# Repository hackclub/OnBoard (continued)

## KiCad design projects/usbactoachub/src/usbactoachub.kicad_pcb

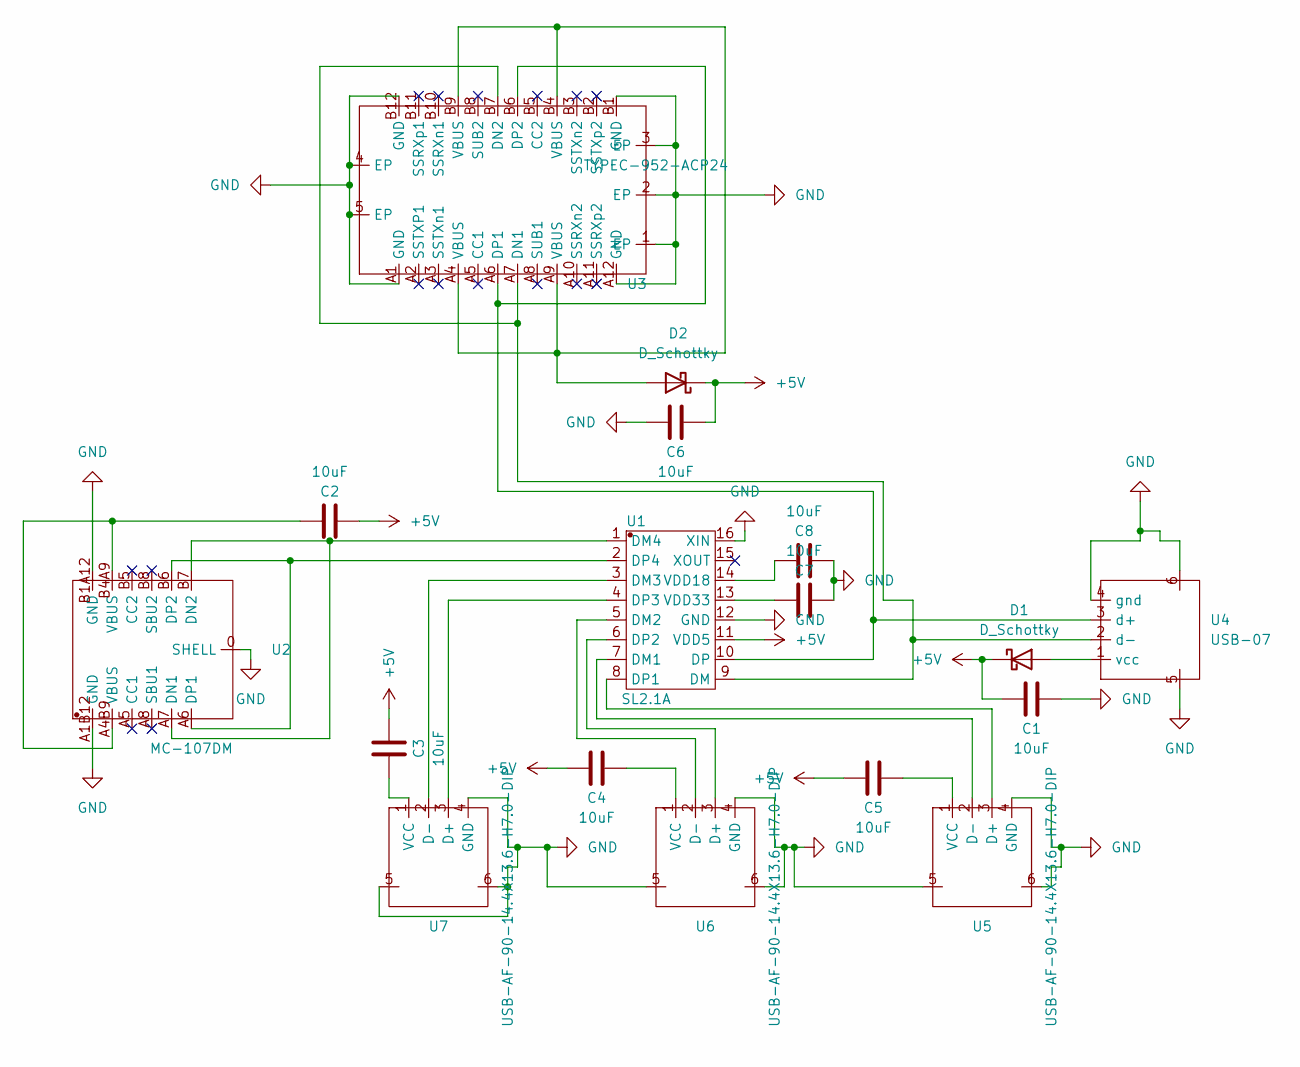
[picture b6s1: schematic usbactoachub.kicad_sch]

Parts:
C1, C2, C3, C4, C5, C6, C7, C8: 10uF; C0603; LCSC Part # C19702
D1, D2: D_Schottky; SOD-323_L1.8-W1.3-LS2.5-RD; LCSC Part # C48192
U1: SL2.1A; SOP-16_L10.0-W3.9-P1.27-LS6.0-BL; LCSC Part # C192893
U2: MC-107DM; USB-C-SMD_MC-107DM; LCSC Part # C2874569
U3: TYPEC-952-ACP24; USB-C-SMD_TYPEC-952-ACP24; LCSC Part # C2840398
U4: USB-07; USB-A-SMD_USB-07; LCSC Part # C183610
U5, U6, U7: USB-AF-90-14.4X13.6-H7.0-DIP; USB-A-TH_C46407; LCSC Part # C46407

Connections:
+5V: C1.2, C2.2, C3.1, C4.2, C5.2, C6.1, D1.1 (K), D2.1 (K), U1.11 (VDD5)
GND: C1.1, C6.2, C7.2, C8.2, U1.12 (GND), U1.16 (XIN), U2.0 (SHELL), U2.A1B12 (GND), U2.B1A12 (GND), U3.1 (EP), U3.2 (EP), U3.3 (EP), U3.4 (EP), U3.5 (EP), U3.A1 (GND), U3.A12 (GND), U3.B1 (GND), U3.B12 (GND), U4.4 (gnd), U4.5, U4.6, U5.4 (GND), U5.5, U5.6, U6.4 (GND), U6.5, U6.6, U7.4 (GND), U7.5, U7.6
unnamed: C2.1, U2.A4B9 (VBUS), U2.B4A9 (VBUS)
unnamed: D1.2 (A), U4.1 (vcc)
unnamed: D2.2 (A), U3.A4 (VBUS), U3.A9 (VBUS), U3.B4 (VBUS), U3.B9 (VBUS)
unnamed: U1.7 (DM1), U5.2 (D-)
unnamed: U1.5 (DM2), U6.2 (D-)
unnamed: U1.3 (DM3), U7.2 (D-)
unnamed: U1.1 (DM4), U2.A7 (DN1), U2.B7 (DN2)
unnamed: U1.9 (DM), U3.A7 (DN1), U3.B7 (DN2), U4.2 (d-)
unnamed: U1.8 (DP1), U5.3 (D+)
unnamed: U1.6 (DP2), U6.3 (D+)
unnamed: U1.4 (DP3), U7.3 (D+)
unnamed: U1.2 (DP4), U2.A6 (DP1), U2.B6 (DP2)
unnamed: U1.10 (DP), U3.A6 (DP1), U3.B6 (DP2), U4.3 (d+)
unnamed: C8.1, U1.14 (VDD18)
unnamed: C7.1, U1.13 (VDD33)
unnamed: C5.1, U5.1 (VCC)
unnamed: C4.1, U6.1 (VCC)
unnamed: C3.2, U7.1 (VCC)

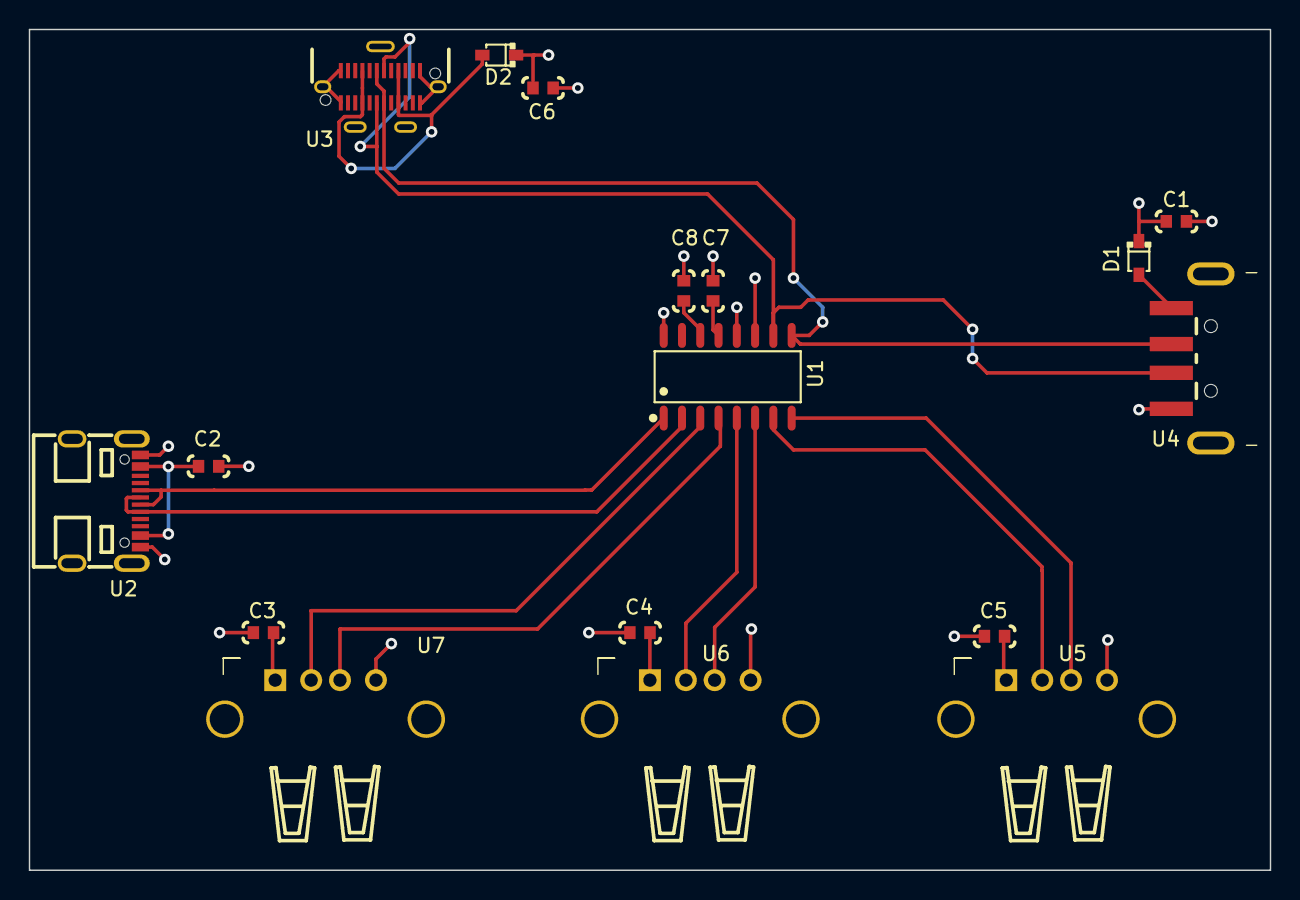
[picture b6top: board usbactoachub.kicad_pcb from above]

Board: 4 copper layers, 86.2 x 58.4 mm, 17 parts (0 on the bottom side), 20 nets.

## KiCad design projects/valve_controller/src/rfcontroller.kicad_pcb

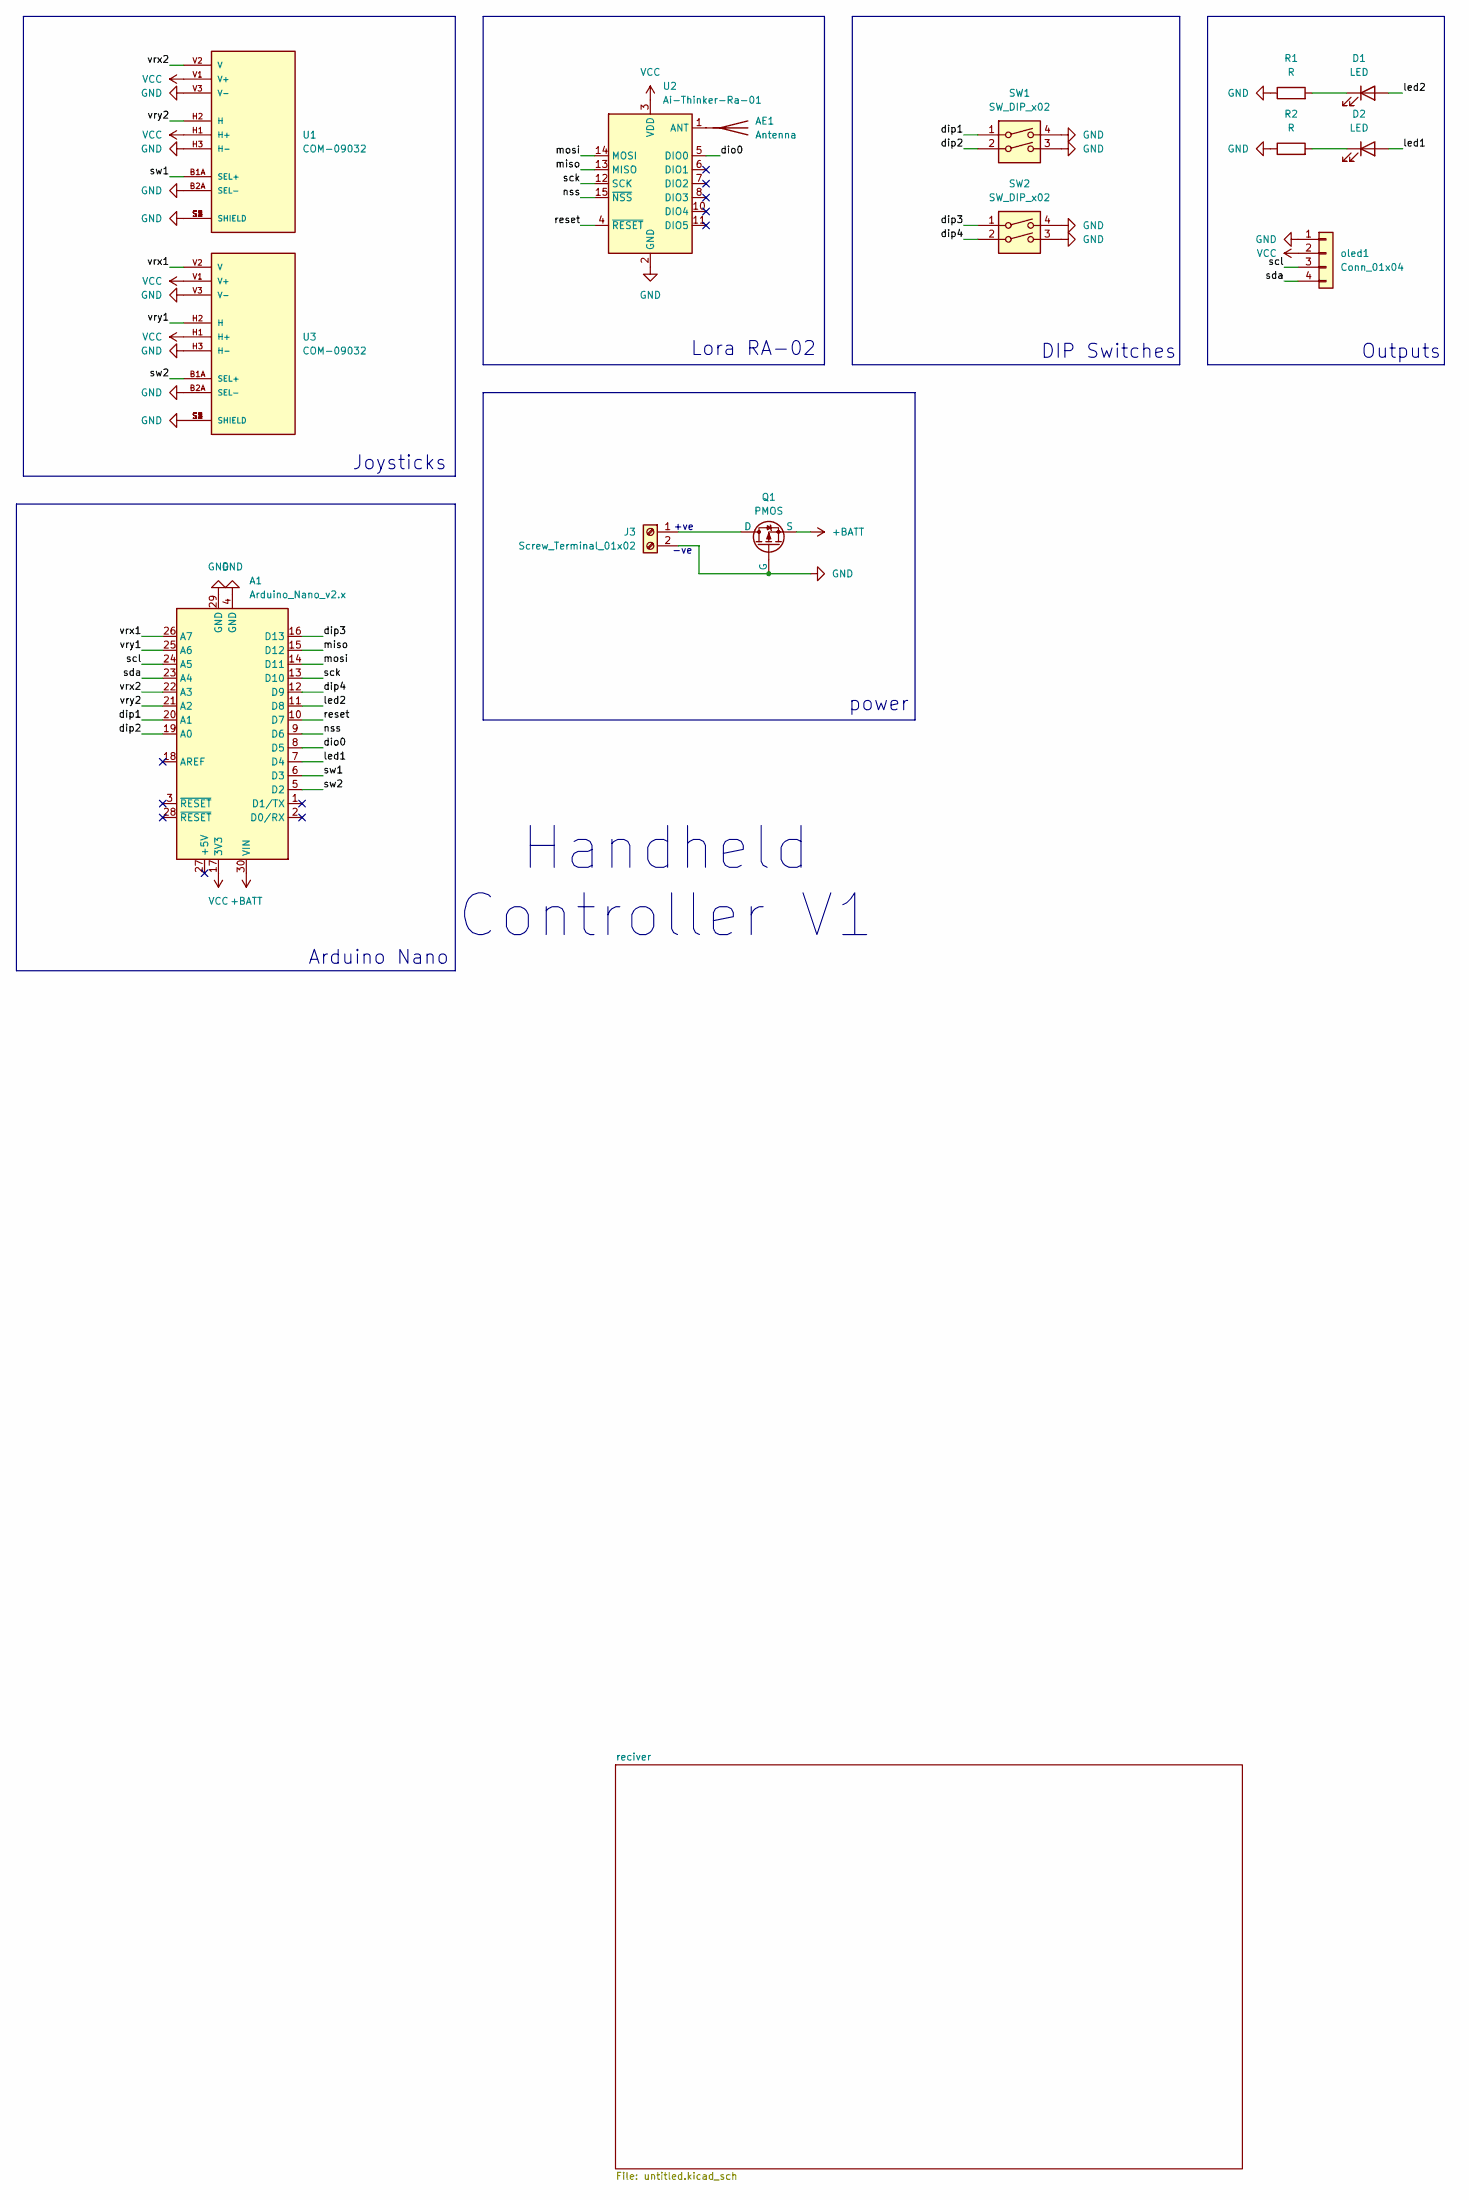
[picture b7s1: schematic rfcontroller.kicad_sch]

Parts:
A1: Arduino_Nano_v2.x; Arduino_Nano
AE1: Antenna; SMA_Amphenol_901-143_Horizontal
D1, D2: LED; LED_D3.0mm
J3: Screw_Terminal_01x02; TerminalBlock_Xinya_XY308-2.54-2P_1x02_P2.54mm_Horizontal
Q1: PMOS; TO-220-3_Vertical
R1, R2: R; R_Axial_DIN0204_L3.6mm_D1.6mm_P5.08mm_Horizontal
SW1, SW2: SW_DIP_x02; SW_DIP_SPSTx02_Slide_9.78x7.26mm_W7.62mm_P2.54mm
U1, U3: COM-09032; XDCR_COM-09032; PARTREV N/A
U2: Ai-Thinker-Ra-01; Ai-Thinker-Ra-01-LoRa_updated
oled1: Conn_01x04; PinHeader_1x04_P2.54mm_Vertical

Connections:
+BATT: A1.30 (VIN), Q1.3 (S)
/dio0: A1.8 (D5), U2.5 (DIO0)
/dip1: A1.20 (A1), SW1.1
/dip2: A1.19 (A0), SW1.2
/dip3: A1.16 (D13), SW2.1
/dip4: A1.12 (D9), SW2.2
/led1: A1.7 (D4), D2.2 (A)
/led2: A1.11 (D8), D1.2 (A)
/miso: A1.15 (D12), U2.13 (MISO)
/mosi: A1.14 (D11), U2.14 (MOSI)
/nss: A1.9 (D6), U2.15 (~NSS)
/reset: A1.10 (D7), U2.4 (~RESET)
/sck: A1.13 (D10), U2.12 (SCK)
/scl: A1.24 (A5), oled1.3
/sda: A1.23 (A4), oled1.4
/sw1: A1.6 (D3), U1.B1A (SEL+)
/sw2: A1.5 (D2), U3.B1A (SEL+)
/vrx1: A1.26 (A7), U3.V2 (V)
/vrx2: A1.22 (A3), U1.V2 (V)
/vry1: A1.25 (A6), U3.H2 (H)
/vry2: A1.21 (A2), U1.H2 (H)
GND: A1.4 (GND), A1.29 (GND), AE1.2, J3.2, Q1.2 (G), R1.1, R2.1, SW1.3, SW1.4, SW2.3, SW2.4, U1.B2A (SEL-), U1.H3 (H-), U1.S1 (SHIELD), U1.S2 (SHIELD), U1.S3 (SHIELD), U1.S4 (SHIELD), U1.V3 (V-), U2.2 (GND), U2.9 (GND), U2.16 (GND), U3.B2A (SEL-), U3.H3 (H-), U3.S1 (SHIELD), U3.S2 (SHIELD), U3.S3 (SHIELD), U3.S4 (SHIELD), U3.V3 (V-), oled1.1
unnamed: AE1.1 (A), U2.1 (ANT)
unnamed: D1.1 (K), R1.2
unnamed: D2.1 (K), R2.2
unnamed: J3.1, Q1.1 (D)
VCC: A1.17 (3V3), U1.H1 (H+), U1.V1 (V+), U2.3 (VDD), U3.H1 (H+), U3.V1 (V+), oled1.2

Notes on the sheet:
-ve
Lora RA-02
power
Joysticks
Handheld Controller V1
+ve
DIP Switches
Outputs
Arduino Nano

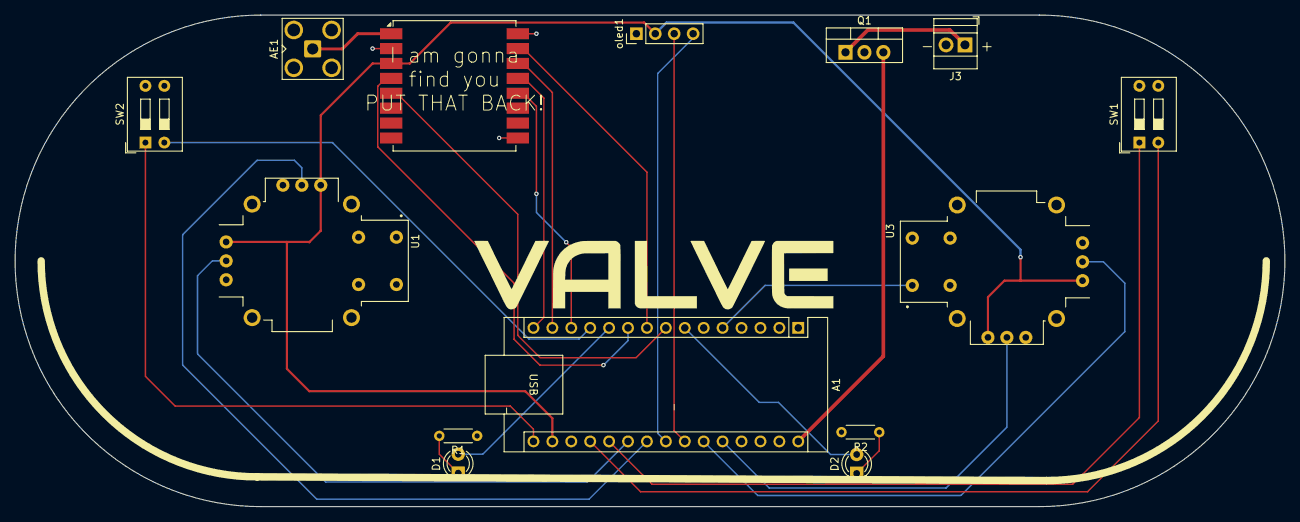
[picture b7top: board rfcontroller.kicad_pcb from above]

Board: 2 copper layers, 170.5 x 66.0 mm, 15 parts (0 on the bottom side), 27 nets.

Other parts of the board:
g: LOGO

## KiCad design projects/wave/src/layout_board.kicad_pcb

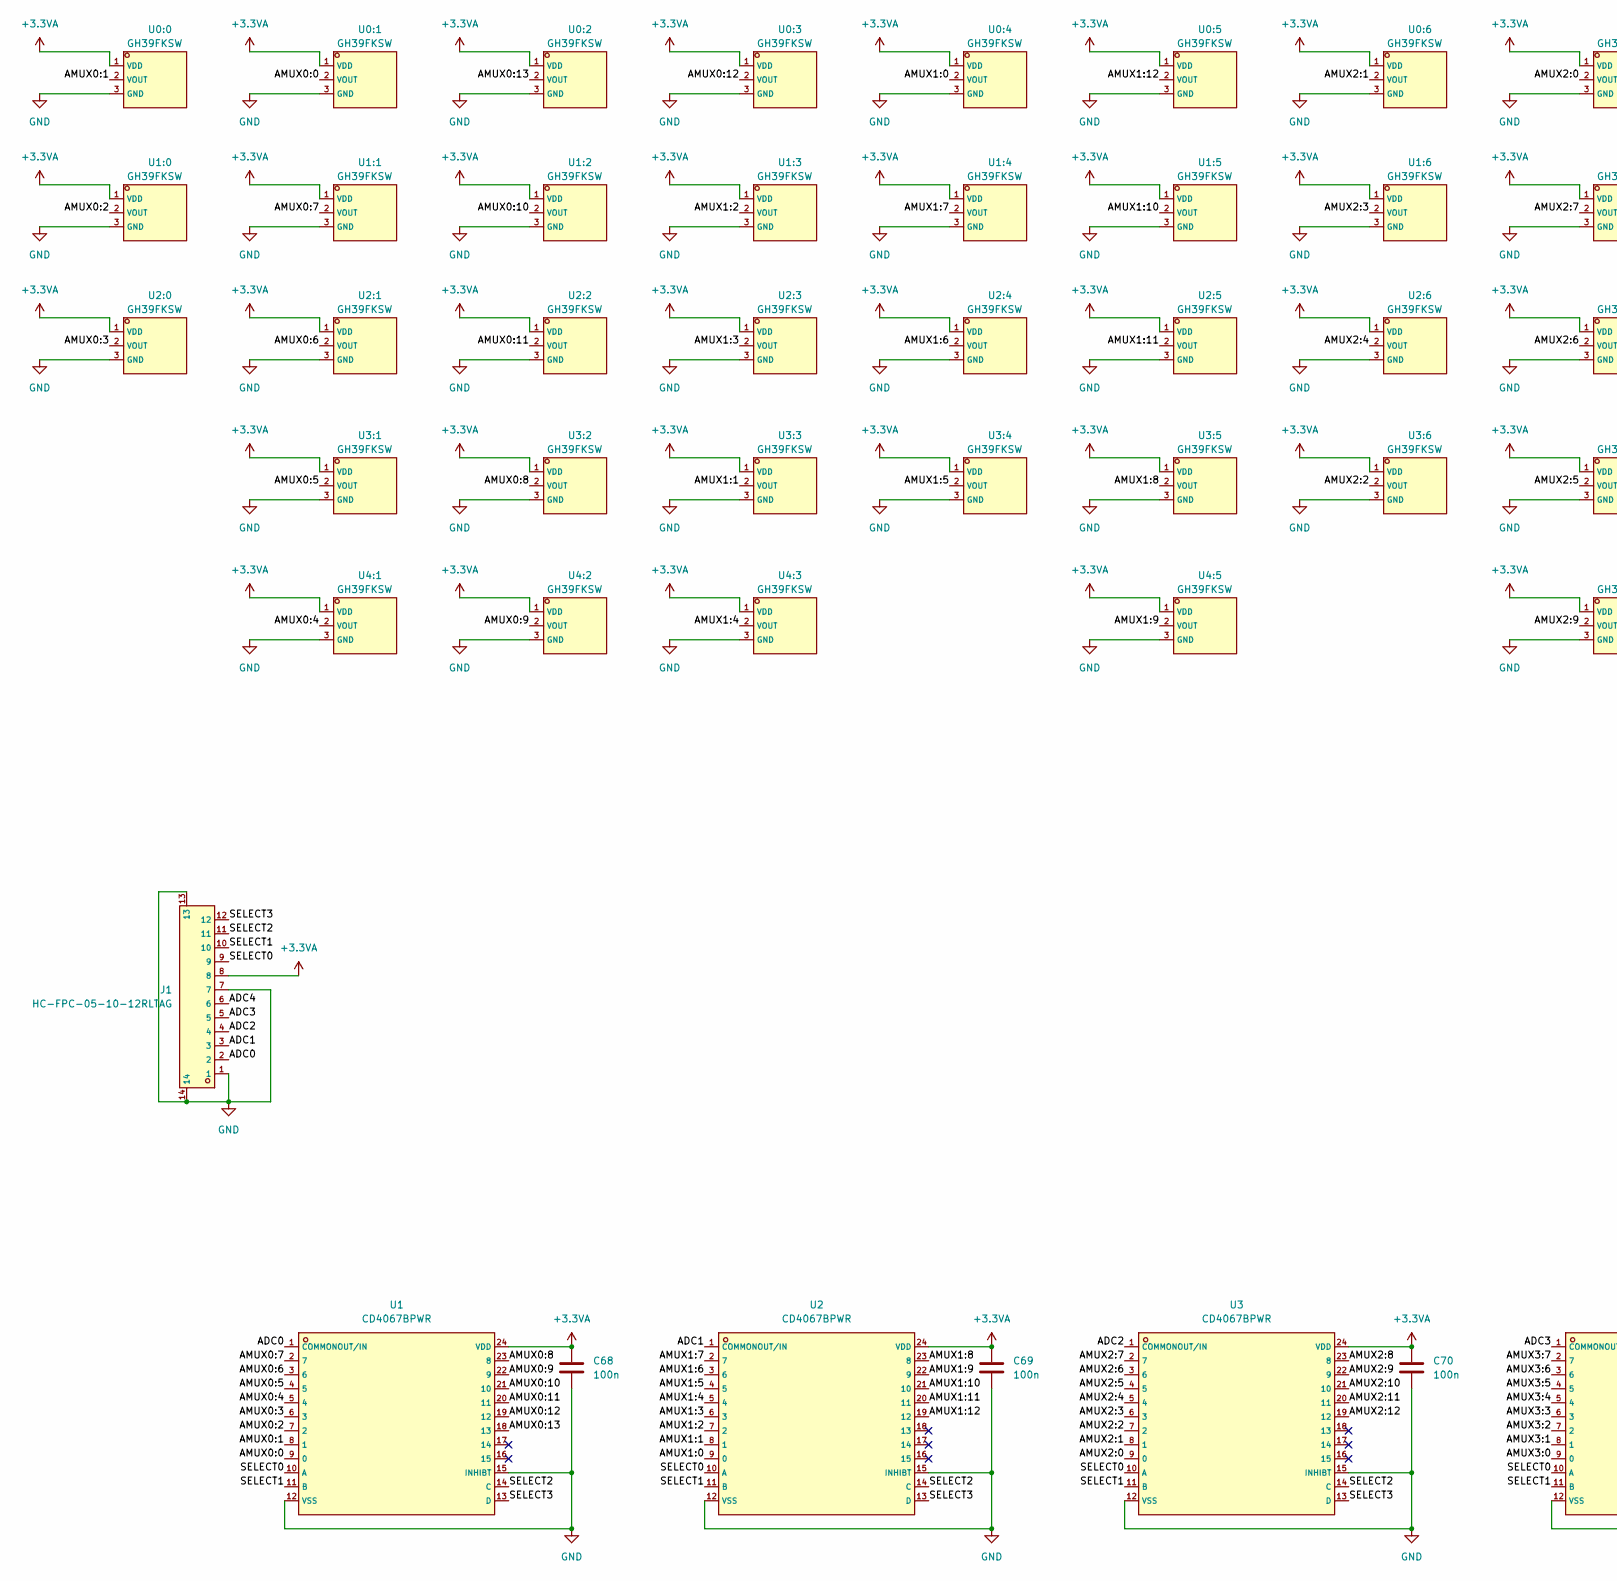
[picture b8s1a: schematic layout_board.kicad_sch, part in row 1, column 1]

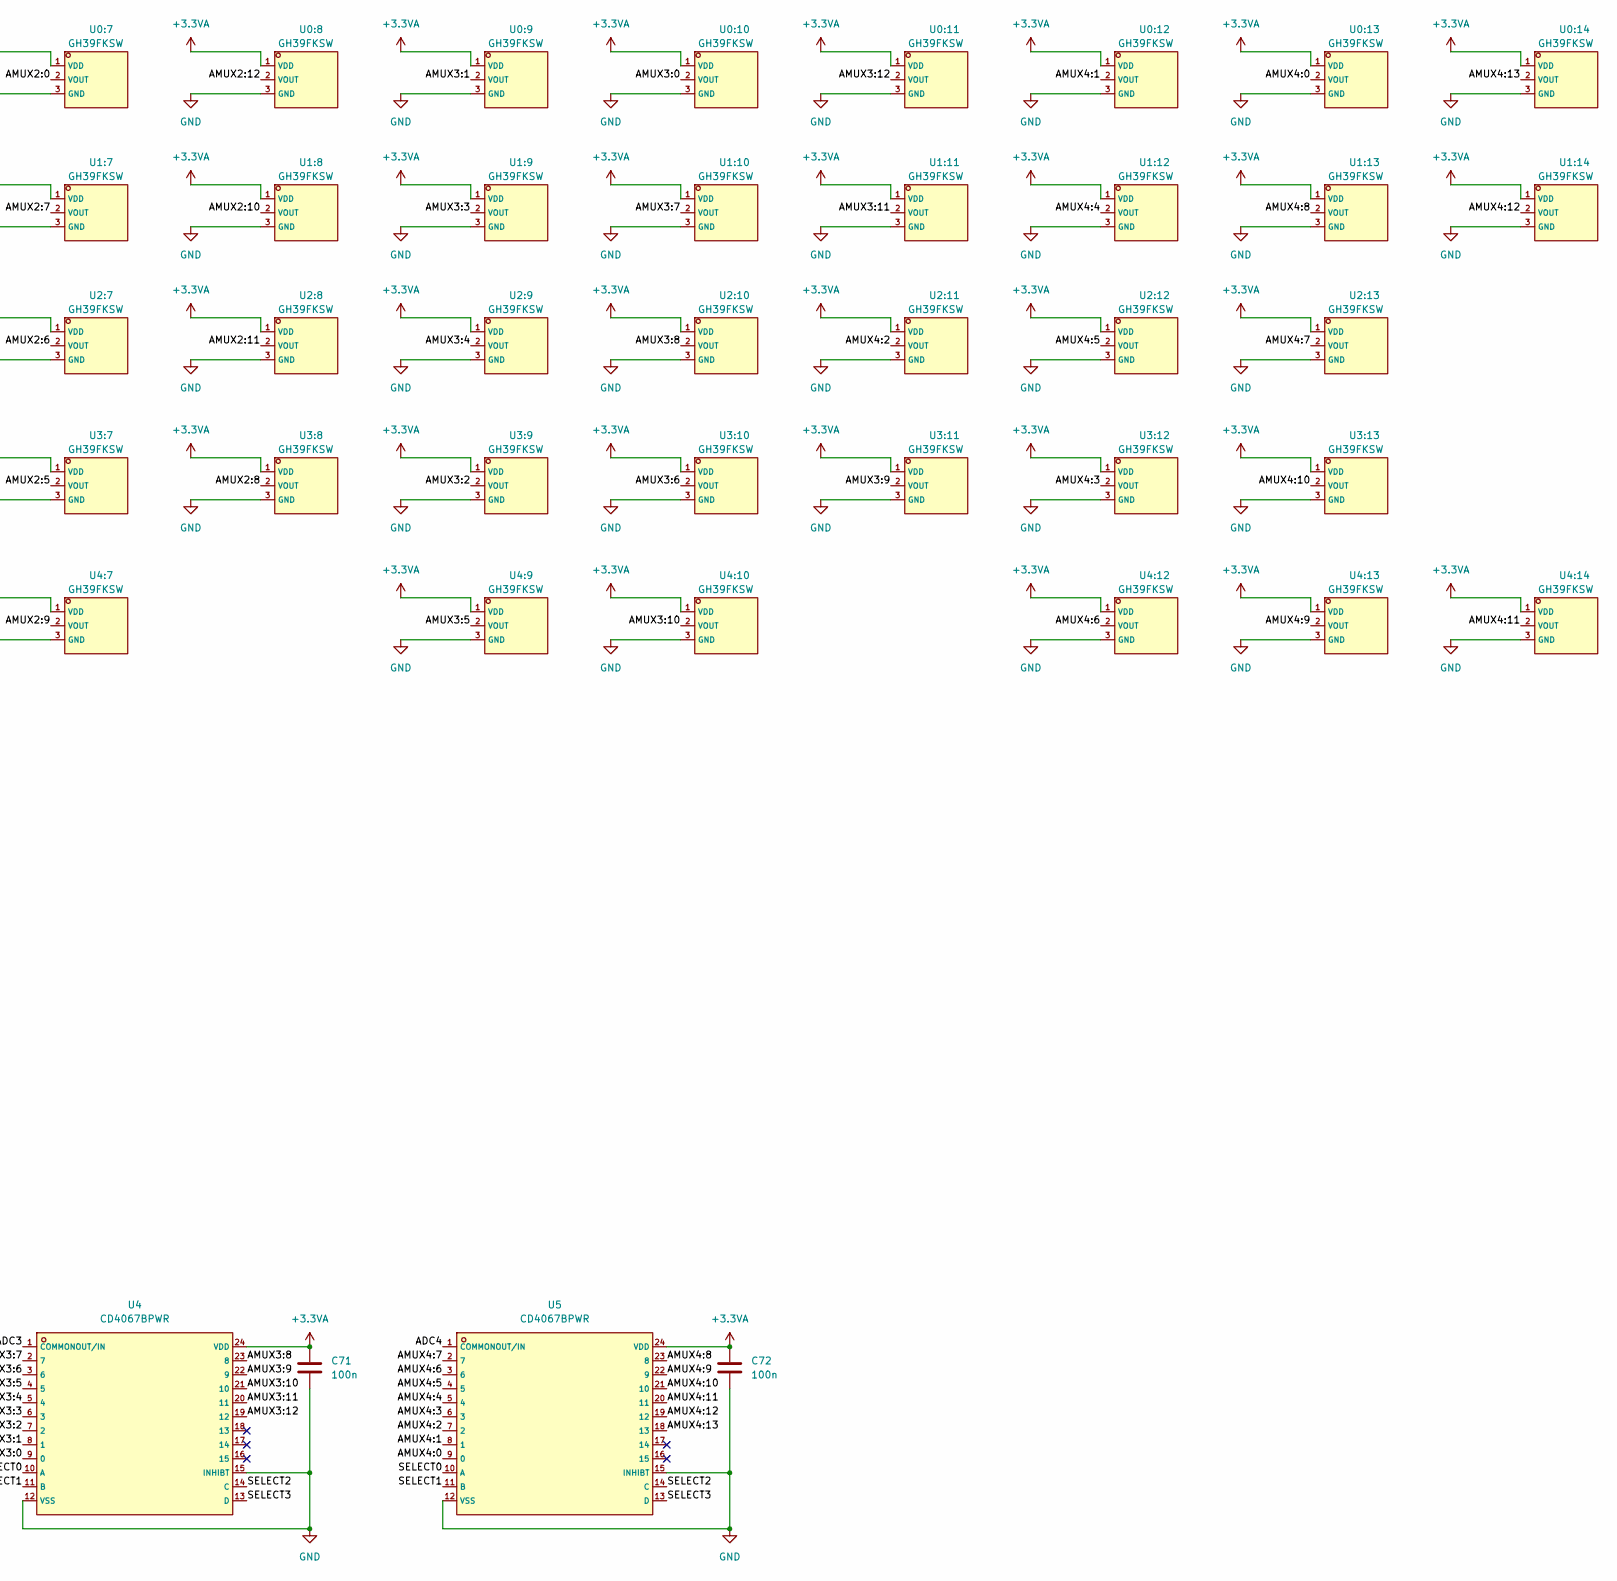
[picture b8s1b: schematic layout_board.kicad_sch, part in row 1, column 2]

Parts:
C68, C69, C70, C71, C72: 100n; C_0402_1005Metric_Pad0.74x0.62mm_HandSolder; LCSC C1525
J1: HC-FPC-05-10-12RLTAG; FPC-SMD_12P-P0.50_HCTL_HC-FPC-05-10-12RLTAG; LCSC C5213732
U0:0, U0:1, U0:2, U0:3, U0:4, U0:5, U0:6, U0:7, U0:8, U0:9, U0:10, U0:11, U0:12, U0:13, U0:14, U1:0, U1:1, U1:2, U1:3, U1:4, U1:5, U1:6, U1:7, U1:8, U1:9, U1:10, U1:11, U1:12, U1:13, U1:14, U2:0, U2:1, U2:2, U2:3, U2:4, U2:5, U2:6, U2:7, U2:8, U2:9, U2:10, U2:11, U2:12, U2:13, U3:1, U3:2, U3:3, U3:4, U3:5, U3:6, U3:7, U3:8, U3:9, U3:10, U3:11, U3:12, U3:13, U4:1, U4:2, U4:3, U4:5, U4:7, U4:9, U4:10, U4:12, U4:13, U4:14: GH39FKSW; SOT-23; LCSC C266230
U1, U2, U3, U4, U5: CD4067BPWR; SSOP-24_5.3x8.2mm_P0.65mm; LCSC C2861251

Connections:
+3.3VA: C68.1, C69.1, C70.1, C71.1, C72.1, J1.8, U0:0.1 (VDD), U0:1.1 (VDD), U0:2.1 (VDD), U0:3.1 (VDD), U0:4.1 (VDD), U0:5.1 (VDD), U0:6.1 (VDD), U0:7.1 (VDD), U0:8.1 (VDD), U0:9.1 (VDD), U0:10.1 (VDD), U0:11.1 (VDD), U0:12.1 (VDD), U0:13.1 (VDD), U0:14.1 (VDD), U1.24 (VDD), U1:0.1 (VDD), U1:1.1 (VDD), U1:2.1 (VDD), U1:3.1 (VDD), U1:4.1 (VDD), U1:5.1 (VDD), U1:6.1 (VDD), U1:7.1 (VDD), U1:8.1 (VDD), U1:9.1 (VDD), U1:10.1 (VDD), U1:11.1 (VDD), U1:12.1 (VDD), U1:13.1 (VDD), U1:14.1 (VDD), U2.24 (VDD), U2:0.1 (VDD), U2:1.1 (VDD), U2:2.1 (VDD), U2:3.1 (VDD), U2:4.1 (VDD), U2:5.1 (VDD), U2:6.1 (VDD), U2:7.1 (VDD), U2:8.1 (VDD), U2:9.1 (VDD), U2:10.1 (VDD), U2:11.1 (VDD), U2:12.1 (VDD), U2:13.1 (VDD), U3.24 (VDD), U3:1.1 (VDD), U3:2.1 (VDD), U3:3.1 (VDD), U3:4.1 (VDD), U3:5.1 (VDD), U3:6.1 (VDD), U3:7.1 (VDD), U3:8.1 (VDD), U3:9.1 (VDD), U3:10.1 (VDD), U3:11.1 (VDD), U3:12.1 (VDD), U3:13.1 (VDD), U4.24 (VDD), U4:1.1 (VDD), U4:2.1 (VDD), U4:3.1 (VDD), U4:5.1 (VDD), U4:7.1 (VDD), U4:9.1 (VDD), U4:10.1 (VDD), U4:12.1 (VDD), U4:13.1 (VDD), U4:14.1 (VDD), U5.24 (VDD)
/ADC0: J1.2, U1.1 (COMMONOUT/IN)
/ADC1: J1.3, U2.1 (COMMONOUT/IN)
/ADC2: J1.4, U3.1 (COMMONOUT/IN)
/ADC3: J1.5, U4.1 (COMMONOUT/IN)
/ADC4: J1.6, U5.1 (COMMONOUT/IN)
/AMUX0:0: U0:1.2 (VOUT), U1.9 (0)
/AMUX0:1: U0:0.2 (VOUT), U1.8 (1)
/AMUX0:2: U1.7 (2), U1:0.2 (VOUT)
/AMUX0:3: U1.6 (3), U2:0.2 (VOUT)
/AMUX0:4: U1.5 (4), U4:1.2 (VOUT)
/AMUX0:5: U1.4 (5), U3:1.2 (VOUT)
/AMUX0:6: U1.3 (6), U2:1.2 (VOUT)
/AMUX0:7: U1.2 (7), U1:1.2 (VOUT)
/AMUX0:8: U1.23 (8), U3:2.2 (VOUT)
/AMUX0:9: U1.22 (9), U4:2.2 (VOUT)
/AMUX0:10: U1.21 (10), U1:2.2 (VOUT)
/AMUX0:11: U1.20 (11), U2:2.2 (VOUT)
/AMUX0:12: U0:3.2 (VOUT), U1.19 (12)
/AMUX0:13: U0:2.2 (VOUT), U1.18 (13)
/AMUX1:0: U0:4.2 (VOUT), U2.9 (0)
/AMUX1:1: U2.8 (1), U3:3.2 (VOUT)
/AMUX1:2: U1:3.2 (VOUT), U2.7 (2)
/AMUX1:3: U2.6 (3), U2:3.2 (VOUT)
/AMUX1:4: U2.5 (4), U4:3.2 (VOUT)
/AMUX1:5: U2.4 (5), U3:4.2 (VOUT)
/AMUX1:6: U2.3 (6), U2:4.2 (VOUT)
/AMUX1:7: U1:4.2 (VOUT), U2.2 (7)
/AMUX1:8: U2.23 (8), U3:5.2 (VOUT)
/AMUX1:9: U2.22 (9), U4:5.2 (VOUT)
/AMUX1:10: U1:5.2 (VOUT), U2.21 (10)
/AMUX1:11: U2.20 (11), U2:5.2 (VOUT)
/AMUX1:12: U0:5.2 (VOUT), U2.19 (12)
/AMUX2:0: U0:7.2 (VOUT), U3.9 (0)
/AMUX2:1: U0:6.2 (VOUT), U3.8 (1)
/AMUX2:2: U3.7 (2), U3:6.2 (VOUT)
/AMUX2:3: U1:6.2 (VOUT), U3.6 (3)
/AMUX2:4: U2:6.2 (VOUT), U3.5 (4)
/AMUX2:5: U3.4 (5), U3:7.2 (VOUT)
/AMUX2:6: U2:7.2 (VOUT), U3.3 (6)
/AMUX2:7: U1:7.2 (VOUT), U3.2 (7)
/AMUX2:8: U3.23 (8), U3:8.2 (VOUT)
/AMUX2:9: U3.22 (9), U4:7.2 (VOUT)
/AMUX2:10: U1:8.2 (VOUT), U3.21 (10)
/AMUX2:11: U2:8.2 (VOUT), U3.20 (11)
/AMUX2:12: U0:8.2 (VOUT), U3.19 (12)
/AMUX3:0: U0:10.2 (VOUT), U4.9 (0)
/AMUX3:1: U0:9.2 (VOUT), U4.8 (1)
/AMUX3:2: U3:9.2 (VOUT), U4.7 (2)
/AMUX3:3: U1:9.2 (VOUT), U4.6 (3)
/AMUX3:4: U2:9.2 (VOUT), U4.5 (4)
/AMUX3:5: U4.4 (5), U4:9.2 (VOUT)
/AMUX3:6: U3:10.2 (VOUT), U4.3 (6)
/AMUX3:7: U1:10.2 (VOUT), U4.2 (7)
/AMUX3:8: U2:10.2 (VOUT), U4.23 (8)
/AMUX3:9: U3:11.2 (VOUT), U4.22 (9)
/AMUX3:10: U4.21 (10), U4:10.2 (VOUT)
/AMUX3:11: U1:11.2 (VOUT), U4.20 (11)
/AMUX3:12: U0:11.2 (VOUT), U4.19 (12)
/AMUX4:0: U0:13.2 (VOUT), U5.9 (0)
/AMUX4:1: U0:12.2 (VOUT), U5.8 (1)
/AMUX4:2: U2:11.2 (VOUT), U5.7 (2)
/AMUX4:3: U3:12.2 (VOUT), U5.6 (3)
/AMUX4:4: U1:12.2 (VOUT), U5.5 (4)
/AMUX4:5: U2:12.2 (VOUT), U5.4 (5)
/AMUX4:6: U4:12.2 (VOUT), U5.3 (6)
/AMUX4:7: U2:13.2 (VOUT), U5.2 (7)
/AMUX4:8: U1:13.2 (VOUT), U5.23 (8)
/AMUX4:9: U4:13.2 (VOUT), U5.22 (9)
/AMUX4:10: U3:13.2 (VOUT), U5.21 (10)
/AMUX4:11: U4:14.2 (VOUT), U5.20 (11)
/AMUX4:12: U1:14.2 (VOUT), U5.19 (12)
/AMUX4:13: U0:14.2 (VOUT), U5.18 (13)
/SELECT0: J1.9, U1.10 (A), U2.10 (A), U3.10 (A), U4.10 (A), U5.10 (A)
/SELECT1: J1.10, U1.11 (B), U2.11 (B), U3.11 (B), U4.11 (B), U5.11 (B)
/SELECT2: J1.11, U1.14 (C), U2.14 (C), U3.14 (C), U4.14 (C), U5.14 (C)
/SELECT3: J1.12, U1.13 (D), U2.13 (D), U3.13 (D), U4.13 (D), U5.13 (D)
GND: C68.2, C69.2, C70.2, C71.2, C72.2, J1.1, J1.7, J1.13, J1.14, U0:0.3 (GND), U0:1.3 (GND), U0:2.3 (GND), U0:3.3 (GND), U0:4.3 (GND), U0:5.3 (GND), U0:6.3 (GND), U0:7.3 (GND), U0:8.3 (GND), U0:9.3 (GND), U0:10.3 (GND), U0:11.3 (GND), U0:12.3 (GND), U0:13.3 (GND), U0:14.3 (GND), U1.12 (VSS), U1.15 (INHIBT), U1:0.3 (GND), U1:1.3 (GND), U1:2.3 (GND), U1:3.3 (GND), U1:4.3 (GND), U1:5.3 (GND), U1:6.3 (GND), U1:7.3 (GND), U1:8.3 (GND), U1:9.3 (GND), U1:10.3 (GND), U1:11.3 (GND), U1:12.3 (GND), U1:13.3 (GND), U1:14.3 (GND), U2.12 (VSS), U2.15 (INHIBT), U2:0.3 (GND), U2:1.3 (GND), U2:2.3 (GND), U2:3.3 (GND), U2:4.3 (GND), U2:5.3 (GND), U2:6.3 (GND), U2:7.3 (GND), U2:8.3 (GND), U2:9.3 (GND), U2:10.3 (GND), U2:11.3 (GND), U2:12.3 (GND), U2:13.3 (GND), U3.12 (VSS), U3.15 (INHIBT), U3:1.3 (GND), U3:2.3 (GND), U3:3.3 (GND), U3:4.3 (GND), U3:5.3 (GND), U3:6.3 (GND), U3:7.3 (GND), U3:8.3 (GND), U3:9.3 (GND), U3:10.3 (GND), U3:11.3 (GND), U3:12.3 (GND), U3:13.3 (GND), U4.12 (VSS), U4.15 (INHIBT), U4:1.3 (GND), U4:2.3 (GND), U4:3.3 (GND), U4:5.3 (GND), U4:7.3 (GND), U4:9.3 (GND), U4:10.3 (GND), U4:12.3 (GND), U4:13.3 (GND), U4:14.3 (GND), U5.12 (VSS), U5.15 (INHIBT)

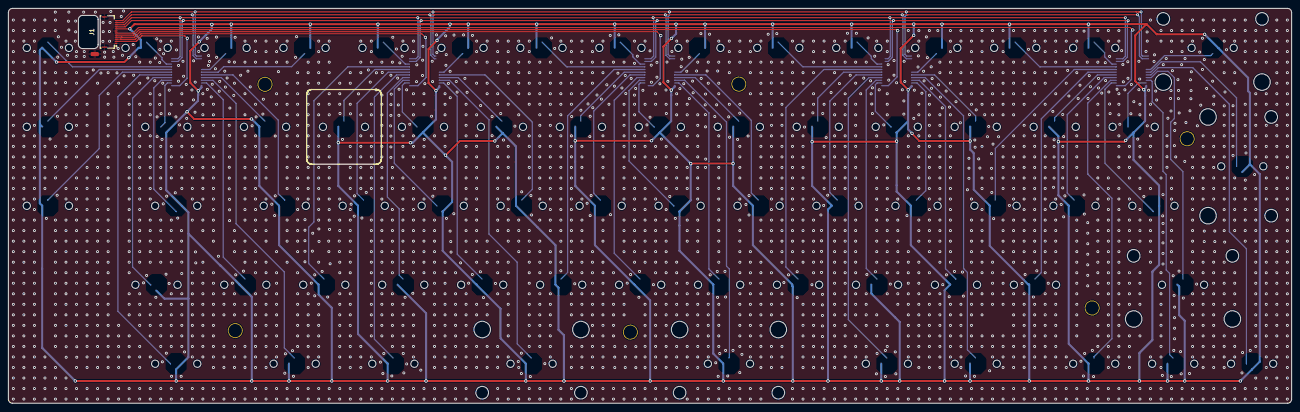
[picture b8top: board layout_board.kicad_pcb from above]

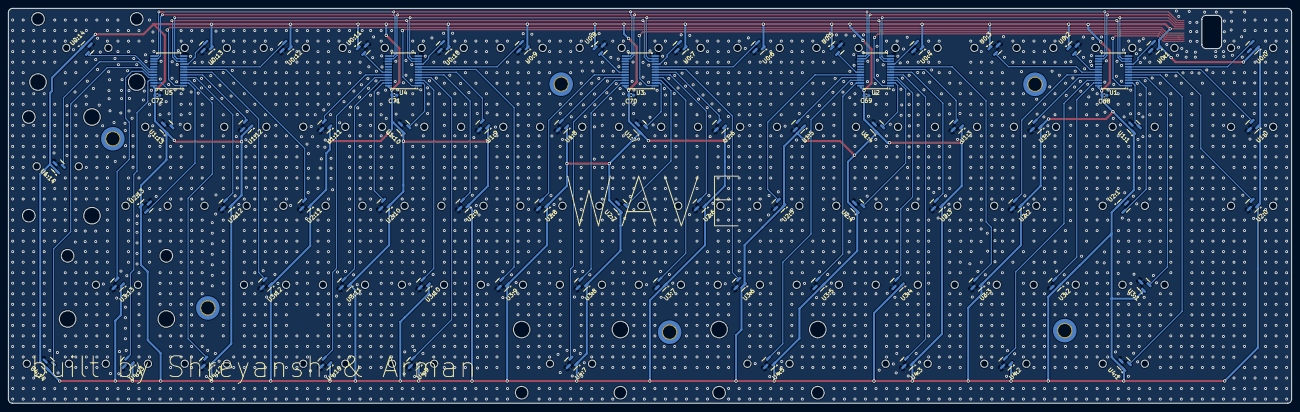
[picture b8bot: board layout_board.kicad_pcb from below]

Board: 2 copper layers, 309.6 x 95.2 mm, 78 parts (77 on the bottom side), 78 nets.

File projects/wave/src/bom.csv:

Designator,Footprint,Quantity,Value,LCSC Part #
"C68, C69, C70, C71, C72",0402,5,100n,C1525
J1,FPC-SMD_12P-P0.50_HCTL_HC-FPC-05-10-12RLTAG,1,HC-FPC-05-10-12RLTAG,C5213732
"U0:0, U0:1, U0:10, U0:11, U0:12, U0:13, U0:14, U0:2, U0:3, U0:4, U0:5, U0:6, U0:7, U0:8, U0:9, U1:0, U1:1, U1:10, U1:11, U1:12, U1:13, U1:14, U1:2, U1:3, U1:4, U1:5, U1:6, U1:7, U1:8, U1:9, U2:0, U2:1, U2:10, U2:11, U2:12, U2:13, U2:2, U2:3, U2:4, U2:5, U2:6, U2:7, U2:8, U2:9, U3:1, U3:10, U3:11, U3:12, U3:13, U3:2, U3:3, U3:4, U3:5, U3:6, U3:7, U3:8, U3:9, U4:1, U4:10, U4:12, U4:13, U4:14, U4:2, U4:3, U4:5, U4:7, U4:9",SOT-23,67,GH39FKSW,C266230
"U1, U2, U3, U4, U5",SSOP-24_5.3x8.2mm_P0.65mm,5,CD4067BPWR,C2861251
